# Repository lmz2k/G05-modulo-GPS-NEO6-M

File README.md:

# GRUPO 05 - Módulo GPS NEO6-M

O projeto consiste em utilizar o arduíno UNO para controlar os módulos GPS NEO6-M e GSM SIM800L afim de captar a geolocalização dos gados em tempo real. Levando em consideração a importância desse projeto com intuito de que grandes criadores de gado venham ter controle através de seu smartphone de seu rebanho, já que segundo uma reportagem da emissora Band junto com a UOL notícias o aumento do preço da carne está gerando criminalidade no sentido de roubo de gados. Com isso pode-se evitar roubos, ou movimentações indevidas dos gados que se afastam de suas terras.

[Link da notícia](https://www.band.uol.com.br/noticias/com-alta-do-preco-da-carne-roubo-de-gado-cresce-na-zona-rural-16325749)

Participantes:

GABRIEL LIMA

THALLYS NOBRE

RUBEM BARROS

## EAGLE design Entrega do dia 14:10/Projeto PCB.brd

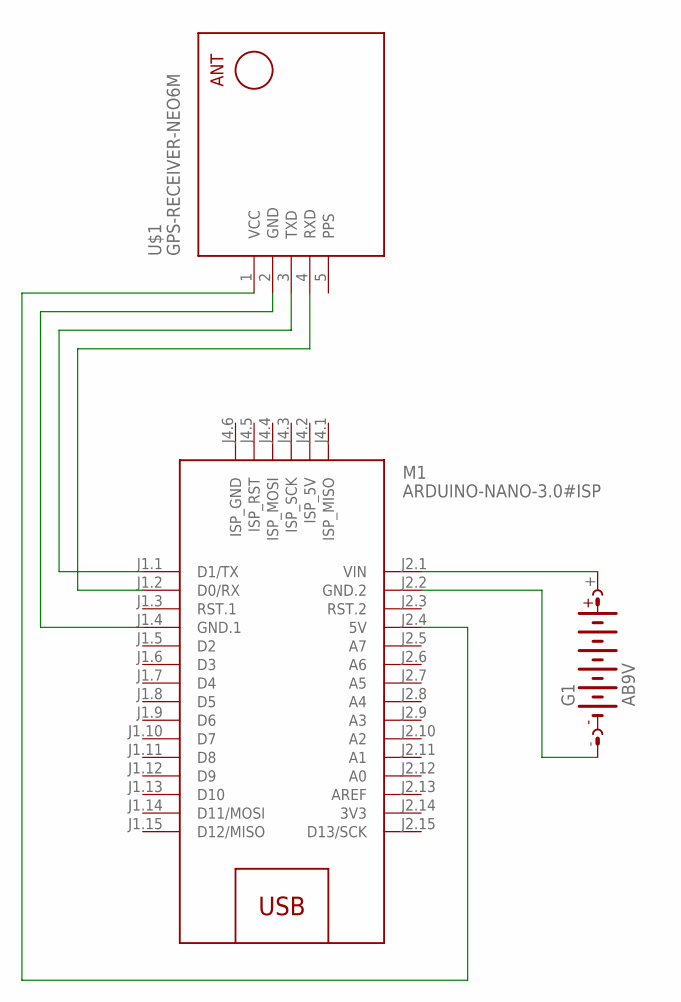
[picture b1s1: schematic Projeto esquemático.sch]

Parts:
G1: AB9V
M1: ARDUINO-NANO-3.0#ISP
U$1: GPS-RECEIVER-NEO6M

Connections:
3V3: M1.J2.14 (3V3)
unnamed: G1.+, M1.J2.1 (VIN)
unnamed: G1.-, M1.J2.2 (GND.2)
unnamed: M1.J2.4 (5V), U$1.1 (VCC)
unnamed: M1.J1.4 (GND.1), U$1.2 (GND)
unnamed: M1.J1.1 (D1/TX), U$1.3 (TXD)
unnamed: M1.J1.2 (D0/RX), U$1.4 (RXD)
PPS: U$1.5 (PPS)

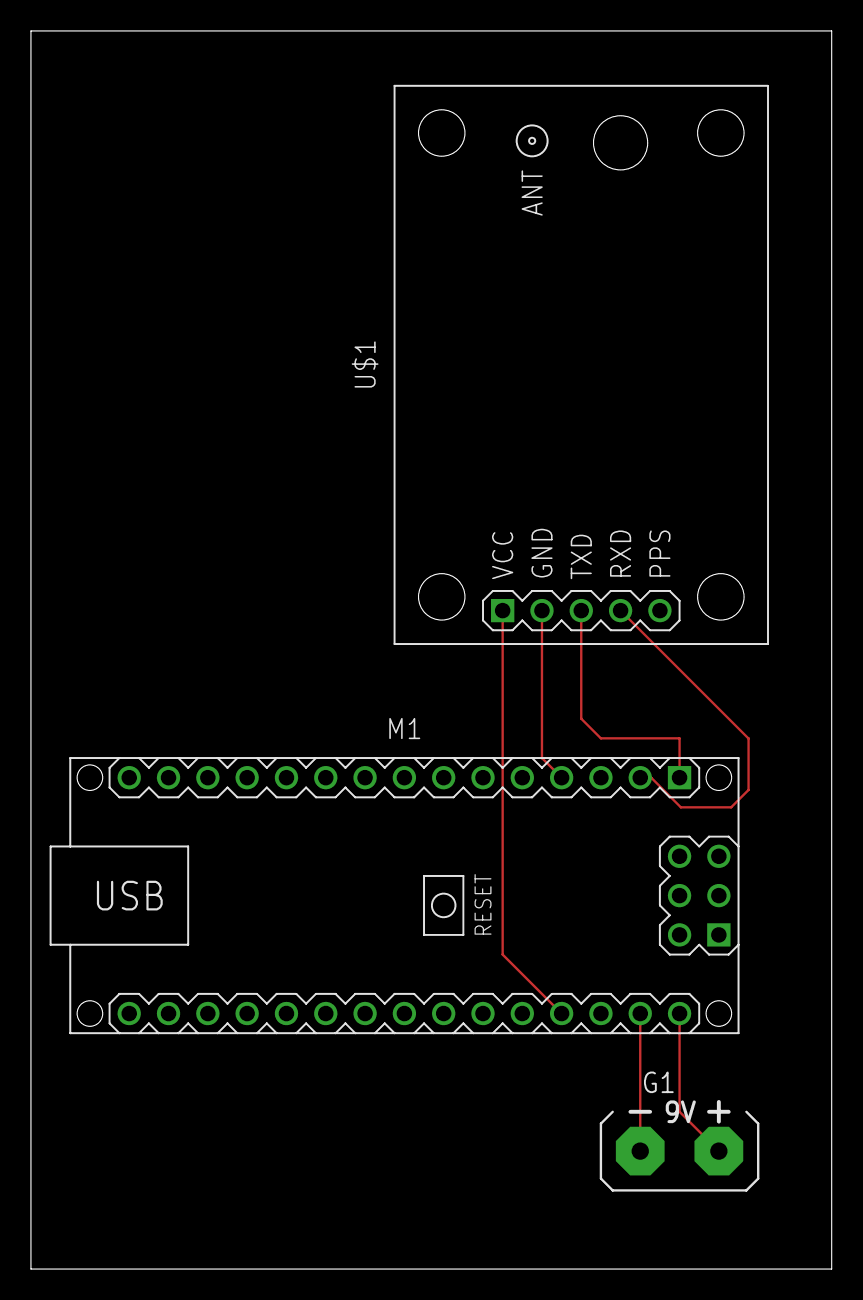
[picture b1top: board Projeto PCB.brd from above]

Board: 2 copper layers, 51.7 x 80.0 mm, 3 parts (0 on the bottom side), 6 nets.

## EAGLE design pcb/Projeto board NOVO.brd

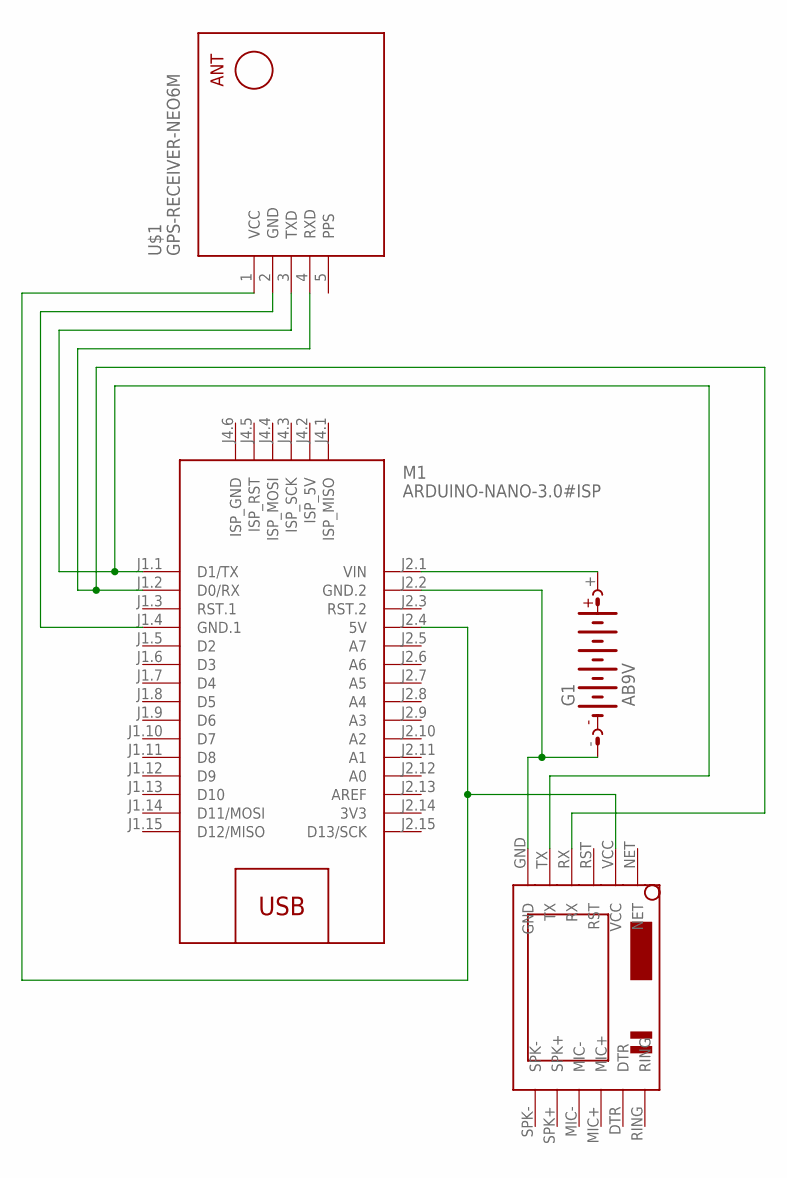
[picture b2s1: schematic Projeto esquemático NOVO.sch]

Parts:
G1: AB9V
M1: ARDUINO-NANO-3.0#ISP
U$1: GPS-RECEIVER-NEO6M
U$2: SIM800LMODULE

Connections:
3V3: M1.J2.14 (3V3)
unnamed: G1.+, M1.J2.1 (VIN)
unnamed: G1.-, M1.J2.2 (GND.2), U$2.GND
unnamed: M1.J2.4 (5V), U$1.1 (VCC), U$2.VCC
unnamed: M1.J1.4 (GND.1), U$1.2 (GND)
unnamed: M1.J1.1 (D1/TX), U$1.3 (TXD), U$2.TX
unnamed: M1.J1.2 (D0/RX), U$1.4 (RXD), U$2.RX
PPS: U$1.5 (PPS)

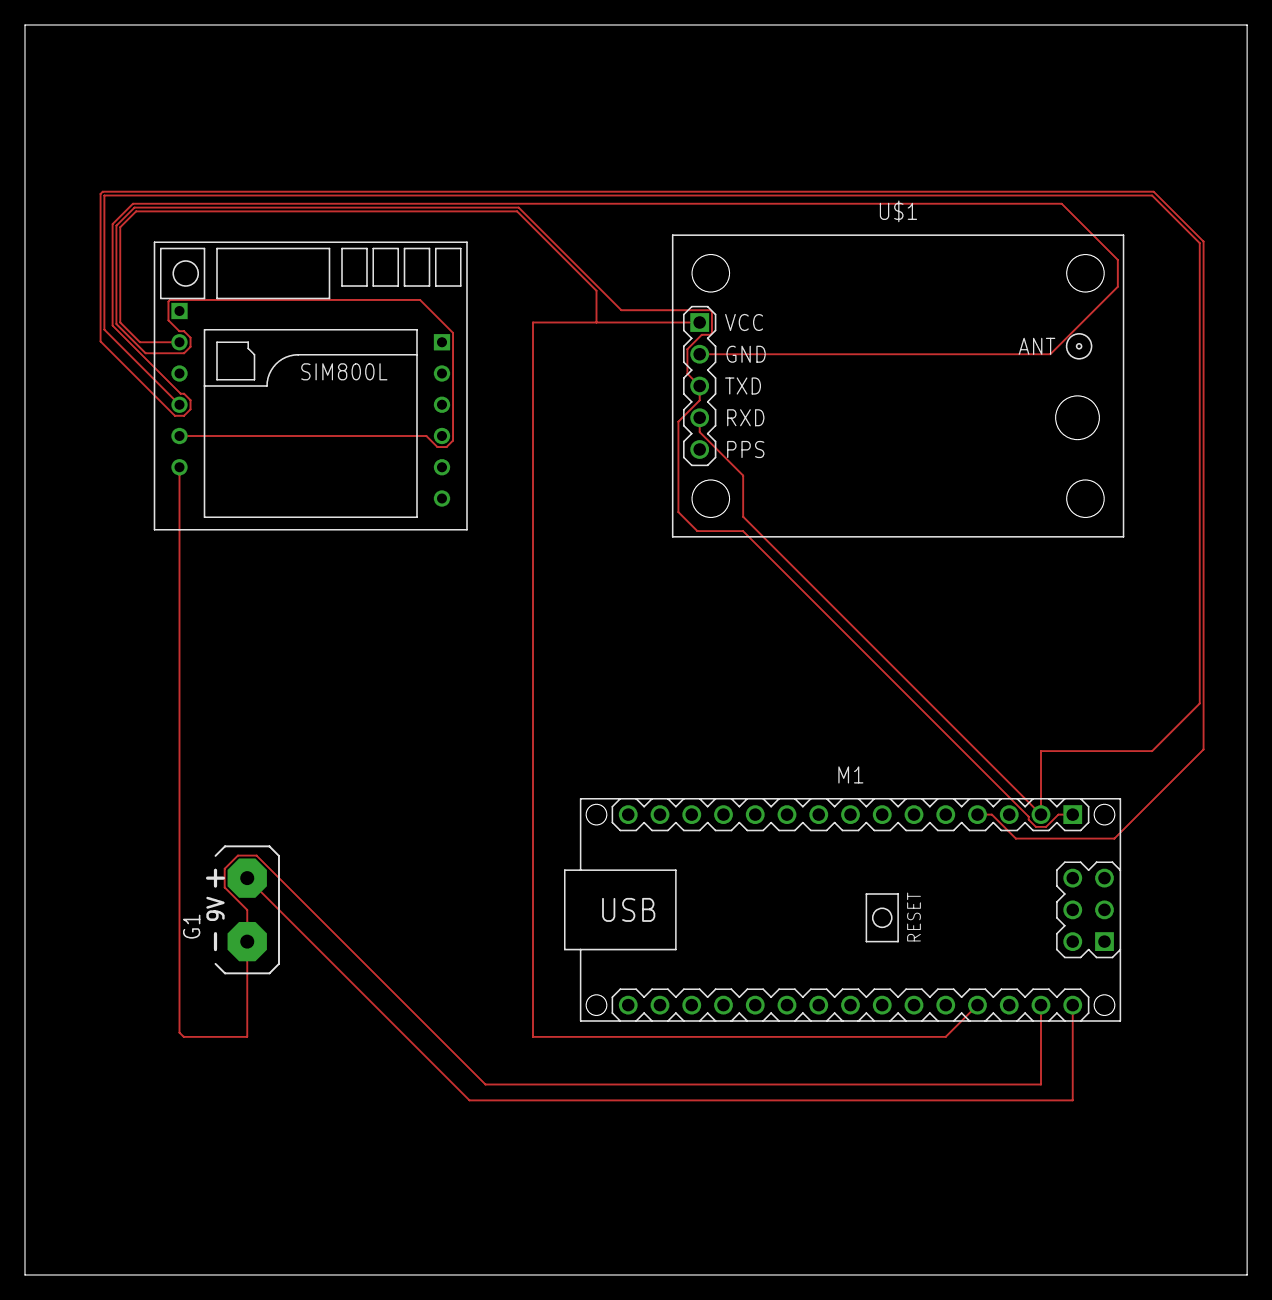
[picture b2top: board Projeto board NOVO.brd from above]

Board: 2 copper layers, 97.8 x 100.0 mm, 4 parts (0 on the bottom side), 6 nets.

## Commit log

2021-08-05 creating files repository
2021-08-05 adding datasheets
2021-10-06 Arquivos da entrega de 06/08 e 14/09
2021-10-10 Atualizando arquivos enviados pelo meet no dia 14/10
2021-10-10 colocando library napasta correta
2021-10-10 Entrega parcial CASE
2021-10-12 Entrega Final
2021-10-12 Entrega final case

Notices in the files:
parts and their libraries:
diy-modules: Released under the Creative Commons Attribution 4.0 International License: http://creativecommons.org/licenses/by/4.0
